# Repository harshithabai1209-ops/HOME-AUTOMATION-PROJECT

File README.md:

# HOME-AUTOMATION-PROJECT(PCB DESIGN)

🏠 IoT-Based Home Automation System
📌 Overview

This project is a Wi-Fi-enabled smart home automation system built using ESP32/ESP8266, IoT protocols, and a custom PCB designed in KiCad.
It allows users to control home appliances (lights, fans, etc.) remotely through a mobile/web dashboard and integrates sensors (temperature, motion, gas, light) for intelligent automation.

🚀 Features

Remote control of AC appliances (fan, light, etc.)

Wi-Fi-based communication (ESP32/ESP8266)

Cloud / MQTT / Blynk / Local server support

Real-time sensor data monitoring

Relay driver circuit with isolation for AC safety

Custom PCB designed in KiCad with proper AC/DC isolation

🛠️ Hardware Components

ESP32 / ESP8266 NodeMCU – Wi-Fi microcontroller

Relay Module (5V/3.3V) – Switching AC loads

DHT11/DHT22 – Temperature & Humidity sensor

PIR Sensor – Motion detection

LDR – Light sensing

MQ-2 Gas Sensor – Safety monitoring

Power Supply – 5V regulated (AMS1117 or buck converter)

Optocoupler & Fuse – Protection for relay section

📐 PCB Design (KiCad)

Designed using KiCad EDA

Separate AC and DC sections for safety

Minimum 3–6 mm isolation gap between high-voltage and low-voltage traces

Solid ground planes for noise reduction

Gerber files generated for PCB manufacturing

⚙️ Software / Firmware

Developed using Arduino IDE / ESP-IDF

Supports:

MQTT (Mosquitto / Cloud broker)

Blynk / ThingsBoard / Custom Web UI

Example firmware features:

Control appliances via mobile app

Read sensor values & push to dashboard

Automation rules (e.g., auto fan ON if temperature > 30°C)

🔌 Circuit Block Diagram
        +-------------------+       +-------------+
        |   ESP32/ESP8266   |------>|  Relay Unit |----> AC Load (Fan/Light)
        +-------------------+       +-------------+
                 |                          |
            +----------+              +----------+
            |  Sensors |              |  Power   |
            +----------+              +----------+

📂 Project Structure
Home-Automation-IoT/
│── hardware/
│   ├── schematics/        # KiCad schematic files
│   ├── pcb-layout/        # PCB design files
│   └── gerbers/           # Manufacturing files
│
│── firmware/
│   ├── main.ino           # Arduino code
│   └── config.h           # Wi-Fi, MQTT, API keys
│
│── docs/
│   ├── README.md          # Project documentation
│   └── images/            # Circuit & PCB renders

🧩 Applications

Smart home & IoT automation

Energy-efficient lighting & appliances

Remote healthcare monitoring (with sensors)

Industrial automation (extended use case)

⚠️ Safety Note

⚡ Caution: This project involves AC mains (230V/110V). Handle with extreme care.
Use proper isolation, fuses, and enclosures while testing.

📖 Future Enhancements

Voice assistant integration (Alexa, Google Assistant)

Mobile app with Flutter/React Native

AI-based predictive automation

Integration with solar energy systems

✨ Made with ❤️ using Embedded Systems + IoT + KiCad

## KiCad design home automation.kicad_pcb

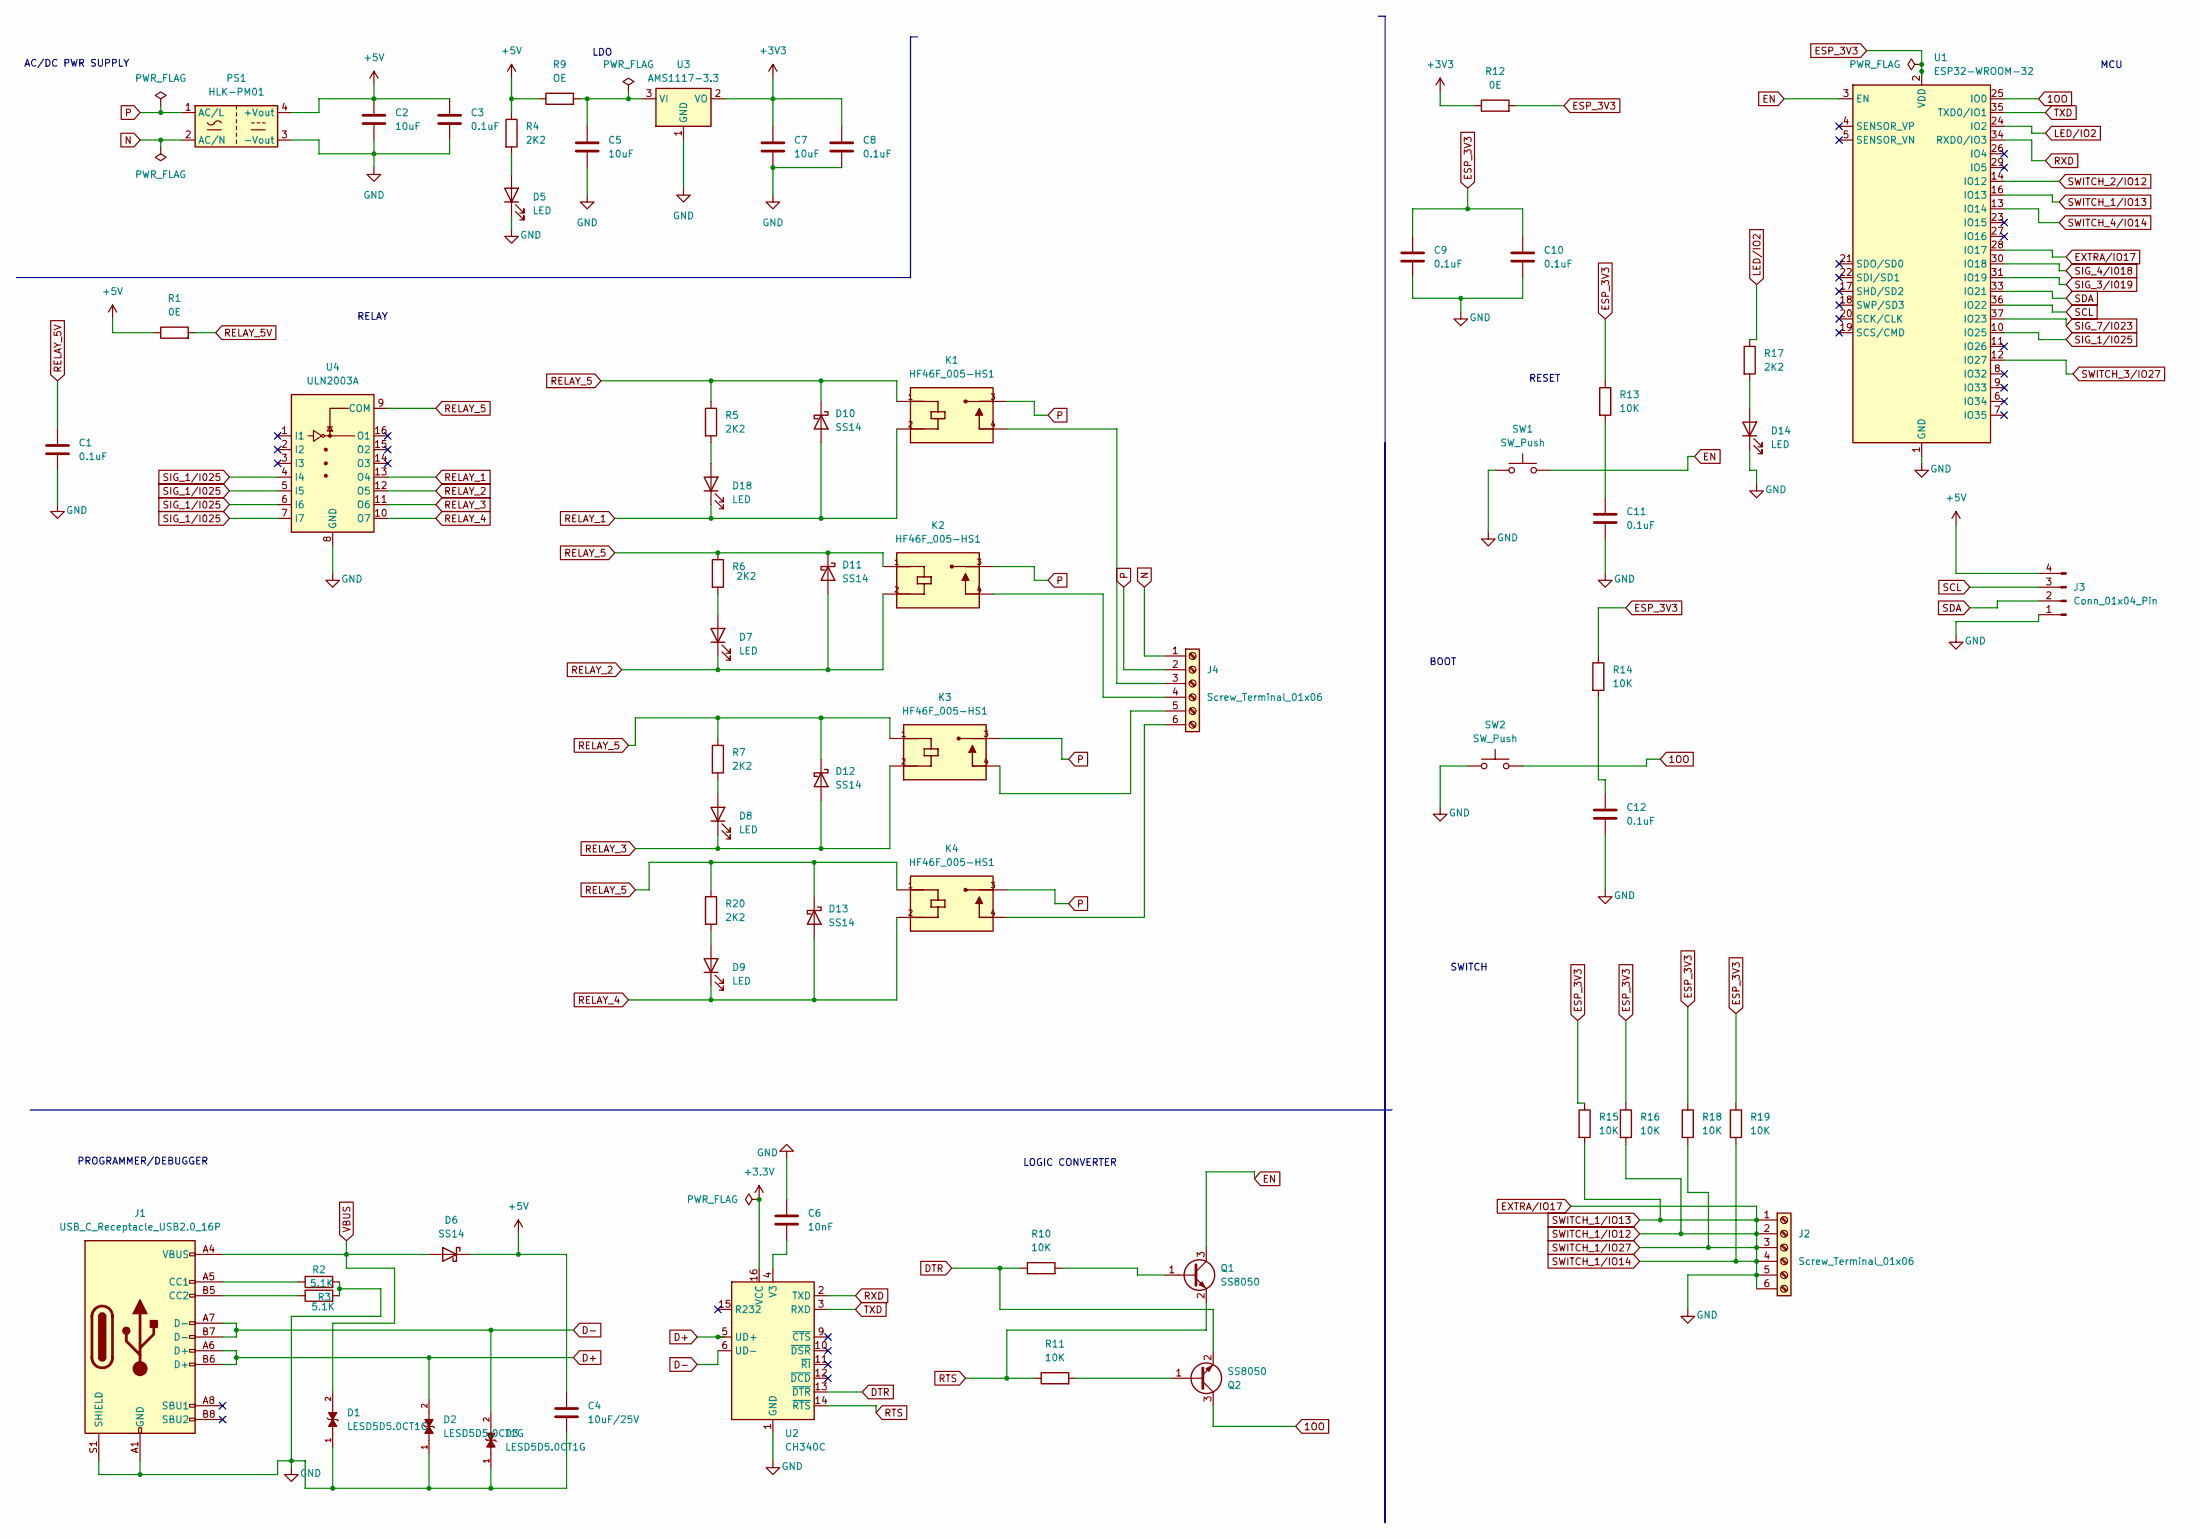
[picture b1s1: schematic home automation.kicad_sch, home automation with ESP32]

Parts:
C1, C3, C8, C9, C10, C11, C12: 0.1uF; C_0603_1608Metric
C2, C5, C7: 10uF; C_1206_3216Metric
C4: 10uF/25V; C_1206_3216Metric
C6: 10nF; C_1206_3216Metric
D1, D2, D3: LESD5D5.0CT1G; TVS_LESD5D5.0CT1G; PARTREV O
D5, D7, D8, D9, D14, D18: LED; LED_0603_1608Metric
D6, D10, D11, D12, D13: SS14; D_SMA
J1: USB_C_Receptacle_USB2.0_16P; USB_C_Receptacle_HCTL_HC-TYPE-C-16P-01A
J2, J4: Screw_Terminal_01x06; TerminalBlock_bornier-6_P5.08mm
J3: Conn_01x04_Pin; PinHeader_1x04_P2.54mm_Vertical
K1, K2, K3, K4: HF46F_005-HS1; RELAY_HF46F_005-HS1; PARTREV 1.00
PS1: HLK-PM01; Converter_ACDC_Hi-Link_HLK-PMxx
Q1, Q2: SS8050; SOT-23
R1, R12: 0E; R_0603_1608Metric
R2, R3: 5.1K; R_0603_1608Metric
R4, R5, R6, R7, R17, R20: 2K2; R_0603_1608Metric
R9: OE; R_0603_1608Metric
R10, R11, R13, R14, R15, R16, R18, R19: 10K; R_0603_1608Metric
SW1, SW2: SW_Push; SW_Push_SPST_NO_Alps_SKRK
U1: ESP32-WROOM-32
U2: CH340C; SOIC-16_3.9x9.9mm_P1.27mm
U3: AMS1117-3.3; SOT-223-3_TabPin2
U4: ULN2003A; SOIC-16_3.9x9.9mm_P1.27mm

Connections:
1OO: Q2.3 (C), SW2.2, U1.25 (IO0)
+3.3V: U2.16 (VCC)
+3V3: C7.1, C8.1, R12.1, U3.2 (VO)
+5V: C2.1, C3.1, C4.1, D6.1 (K), J3.4, PS1.4 (+Vout), R1.1, R4.1, R9.1
D+: D2.2, J1.A6 (D+), J1.B6 (D+), U2.5 (UD+)
D-: D3.2, J1.A7 (D-), J1.B7 (D-), U2.6 (UD-)
DTR: Q2.2 (E), R10.1, U2.13 (~DTR)
EN: Q1.3 (C), SW1.2, U1.3 (EN)
ESP_3V3: C9.1, C10.1, R12.2, R13.1, R14.1, R15.1, R16.1, R18.1, R19.1, U1.2 (VDD)
EXTRA/IO17: C1.2, C2.2, C3.2, C4.2, C5.2, C6.2, C7.2, C8.2, C9.2, C10.2, C11.2, C12.2, D1.1, D2.1, D3.1, D5.1 (K), D14.1 (K), J1.A1 (GND), J1.A12 (GND), J1.B1 (GND), J1.B12 (GND), J1.S1 (SHIELD), J2.1, J2.2, J2.3, J2.4, J2.5, J2.6, J3.1, PS1.3 (-Vout), R2.2, R3.2, R15.2, R16.2, R18.2, R19.2, SW1.1, SW2.1, U1.1 (GND), U1.15 (GND), U1.16 (IO13), U1.28 (IO17), U1.38 (GND), U1.39 (GND), U2.1 (GND), U3.1 (GND), U4.8 (GND)
LED/IO2: R17.1, U1.24 (IO2)
N: J4.1, PS1.2 (AC/N)
unnamed: C11.1, R13.2
unnamed: C12.1, R14.2
unnamed: D5.2 (A), R4.2
unnamed: D7.2 (A), R6.2
unnamed: D8.2 (A), R7.2
unnamed: D9.2 (A), R20.2
unnamed: D14.2 (A), R17.2
unnamed: D18.2 (A), R5.2
unnamed: J1.A5 (CC1), R2.1
unnamed: J1.B5 (CC2), R3.1
unnamed: J4.3, K1.4
unnamed: J4.4, K2.4
unnamed: J4.5, K3.4
unnamed: J4.6, K4.4
unnamed: Q1.1 (B), R10.2
unnamed: Q2.1 (B), R11.2
unnamed: C6.1, U2.4 (V3)
unnamed: C5.1, R9.2, U3.3 (VI)
P: J4.2, K1.3, K2.3, K3.3, K4.3, PS1.1 (AC/L)
RELAY_1: D10.2 (A), D18.1 (K), K1.2, U4.13 (O4)
RELAY_2: D7.1 (K), D11.2 (A), K2.2, U4.12 (O5)
RELAY_3: D8.1 (K), D12.2 (A), K3.2, U4.11 (O6)
RELAY_4: D9.1 (K), D13.2 (A), K4.2, U4.10 (O7)
RELAY_5: D10.1 (K), D11.1 (K), D12.1 (K), D13.1 (K), K1.1, K2.1, K3.1, K4.1, R5.1, R6.1, R7.1, R20.1, U4.9 (COM)
RELAY_5V: C1.1, R1.2
RTS: Q1.2 (E), R11.1, U2.14 (~RTS)
RXD: U1.34 (RXD0/IO3), U2.2 (TXD)
SCL: J3.3, U1.36 (IO22)
SDA: J3.2, U1.33 (IO21)
SIG_1/I025: U1.10 (IO25), U4.4 (I4), U4.5 (I5), U4.6 (I6), U4.7 (I7)
SIG_3/I019: U1.31 (IO19)
SIG_4/I018: U1.30 (IO18)
SIG_7/I023: U1.37 (IO23)
SWITCH_2/IO12: U1.14 (IO12)
SWITCH_3/IO27: U1.12 (IO27)
SWITCH_4/IO14: U1.13 (IO14)
TXD: U1.35 (TXD0/IO1), U2.3 (RXD)
VBUS: D1.2, D6.2 (A), J1.A4 (VBUS), J1.A9 (VBUS), J1.B4 (VBUS), J1.B9 (VBUS)

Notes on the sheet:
AC/DC PWR SUPPLY
LDO
BOOT
RESET
RELAY
PROGRAMMER/DEBUGGER
LOGIC CONVERTER
MCU
SWITCH

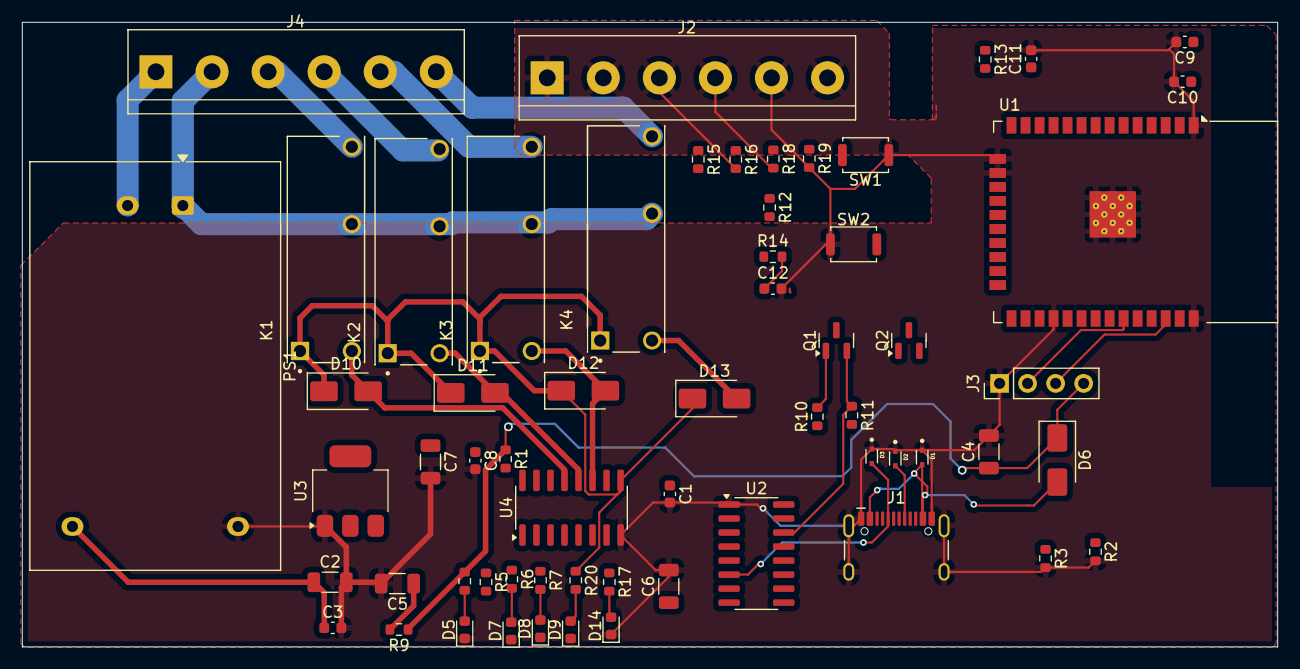
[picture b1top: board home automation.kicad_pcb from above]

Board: 2 copper layers, 113.7 x 56.6 mm, 62 parts (1 on the bottom side), 43 nets.
